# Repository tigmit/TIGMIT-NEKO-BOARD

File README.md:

# TIGMIT NEKO BOARD 

HEY fellow nerd :3
thanks for checking out my project hehe

This is a one man project trying to create (my) ultimate keyboard. taylored to the personal needs of a software developer with a thing for cute and weeby shit... hence the name :P 

the project features 

- 79 keys in a kind of.. compact TKL arrangement.
- a 240 x 240 round Display
- rotary encoder
- analog slider
- fully controllable RGB for each key
- hot swappable switches
- fully custom Firmware (feel free to reuse for your project)
- wireless operation via Bluetooth
- a fully functioal shell with ato completion

to enable the NEKO SHELL go to debugSettings.hpp and enable ```#define DEVMODE ```

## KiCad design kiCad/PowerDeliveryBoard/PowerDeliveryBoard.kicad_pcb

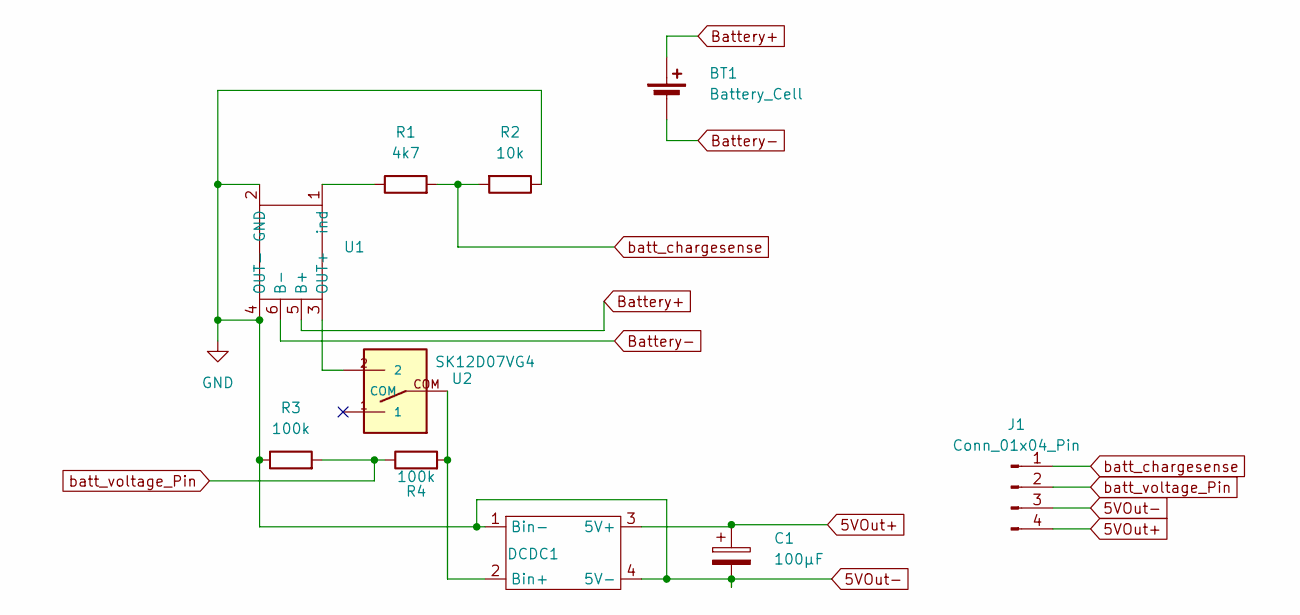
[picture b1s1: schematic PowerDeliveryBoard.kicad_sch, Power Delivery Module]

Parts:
BT1: Battery_Cell; battery solder pins
C1: 100µF; CP_Elec_6.3x5.2
DCDC1: DCDC-Converter
J1: Conn_01x04_Pin; PinHeader_1x04_P2.54mm_Vertical
R1: 4k7; R_Axial_DIN0204_L3.6mm_D1.6mm_P7.62mm_Horizontal
R2: 10k; R_Axial_DIN0204_L3.6mm_D1.6mm_P7.62mm_Horizontal
R3, R4: 100k; R_Axial_DIN0204_L3.6mm_D1.6mm_P7.62mm_Horizontal
U1: TP4056-18650
U2: SK12D07VG4

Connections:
5VOut+: C1.1, DCDC1.3 (5V+), J1.4
5VOut-: C1.2, DCDC1.1 (Bin-), DCDC1.4 (5V-), J1.3, R2.1, R3.1, U1.2 (GND), U1.4 (OUT-)
Battery+: BT1.1 (+), U1.5 (B+)
Battery-: BT1.2 (-), U1.6 (B-)
unnamed: DCDC1.2 (Bin+), R4.2, U2.COM
unnamed: U1.3 (OUT+), U2.2
unnamed: R1.1, U1.1 (ind)
batt_chargesense: J1.1, R1.2, R2.2
batt_voltage_Pin: J1.2, R3.2, R4.1

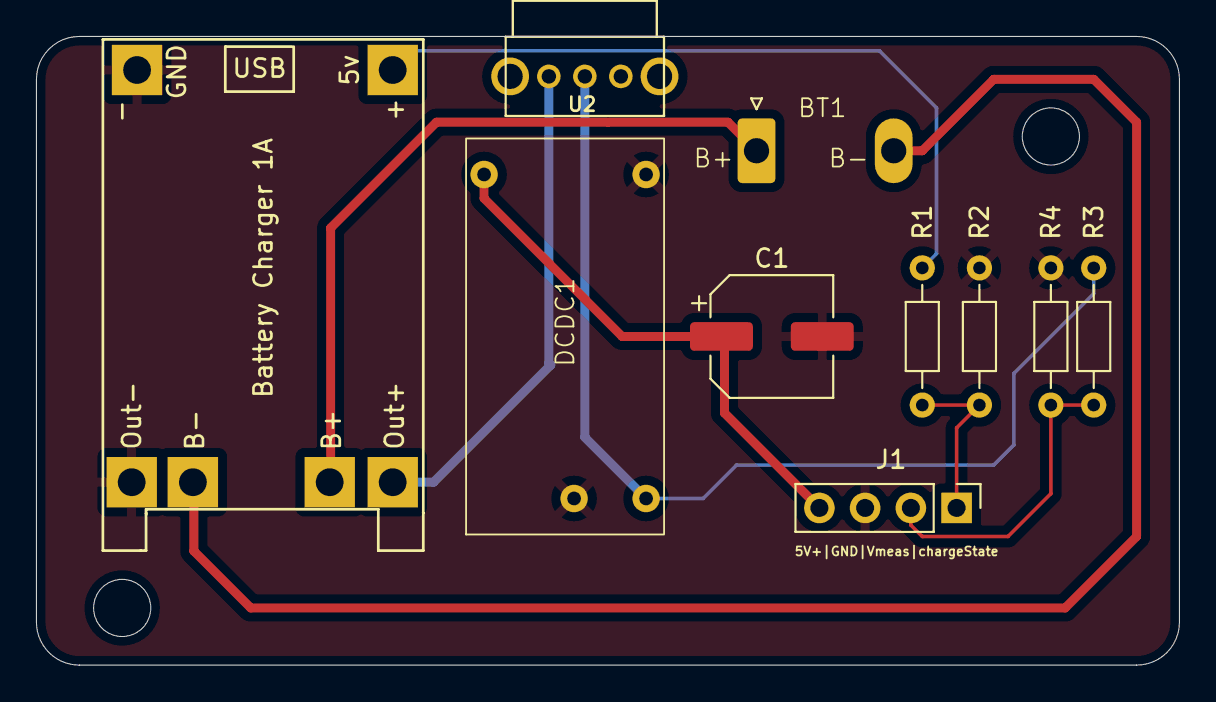
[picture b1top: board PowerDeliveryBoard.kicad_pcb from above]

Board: 2 copper layers, 63.5 x 34.9 mm, 10 parts (0 on the bottom side), 9 nets.

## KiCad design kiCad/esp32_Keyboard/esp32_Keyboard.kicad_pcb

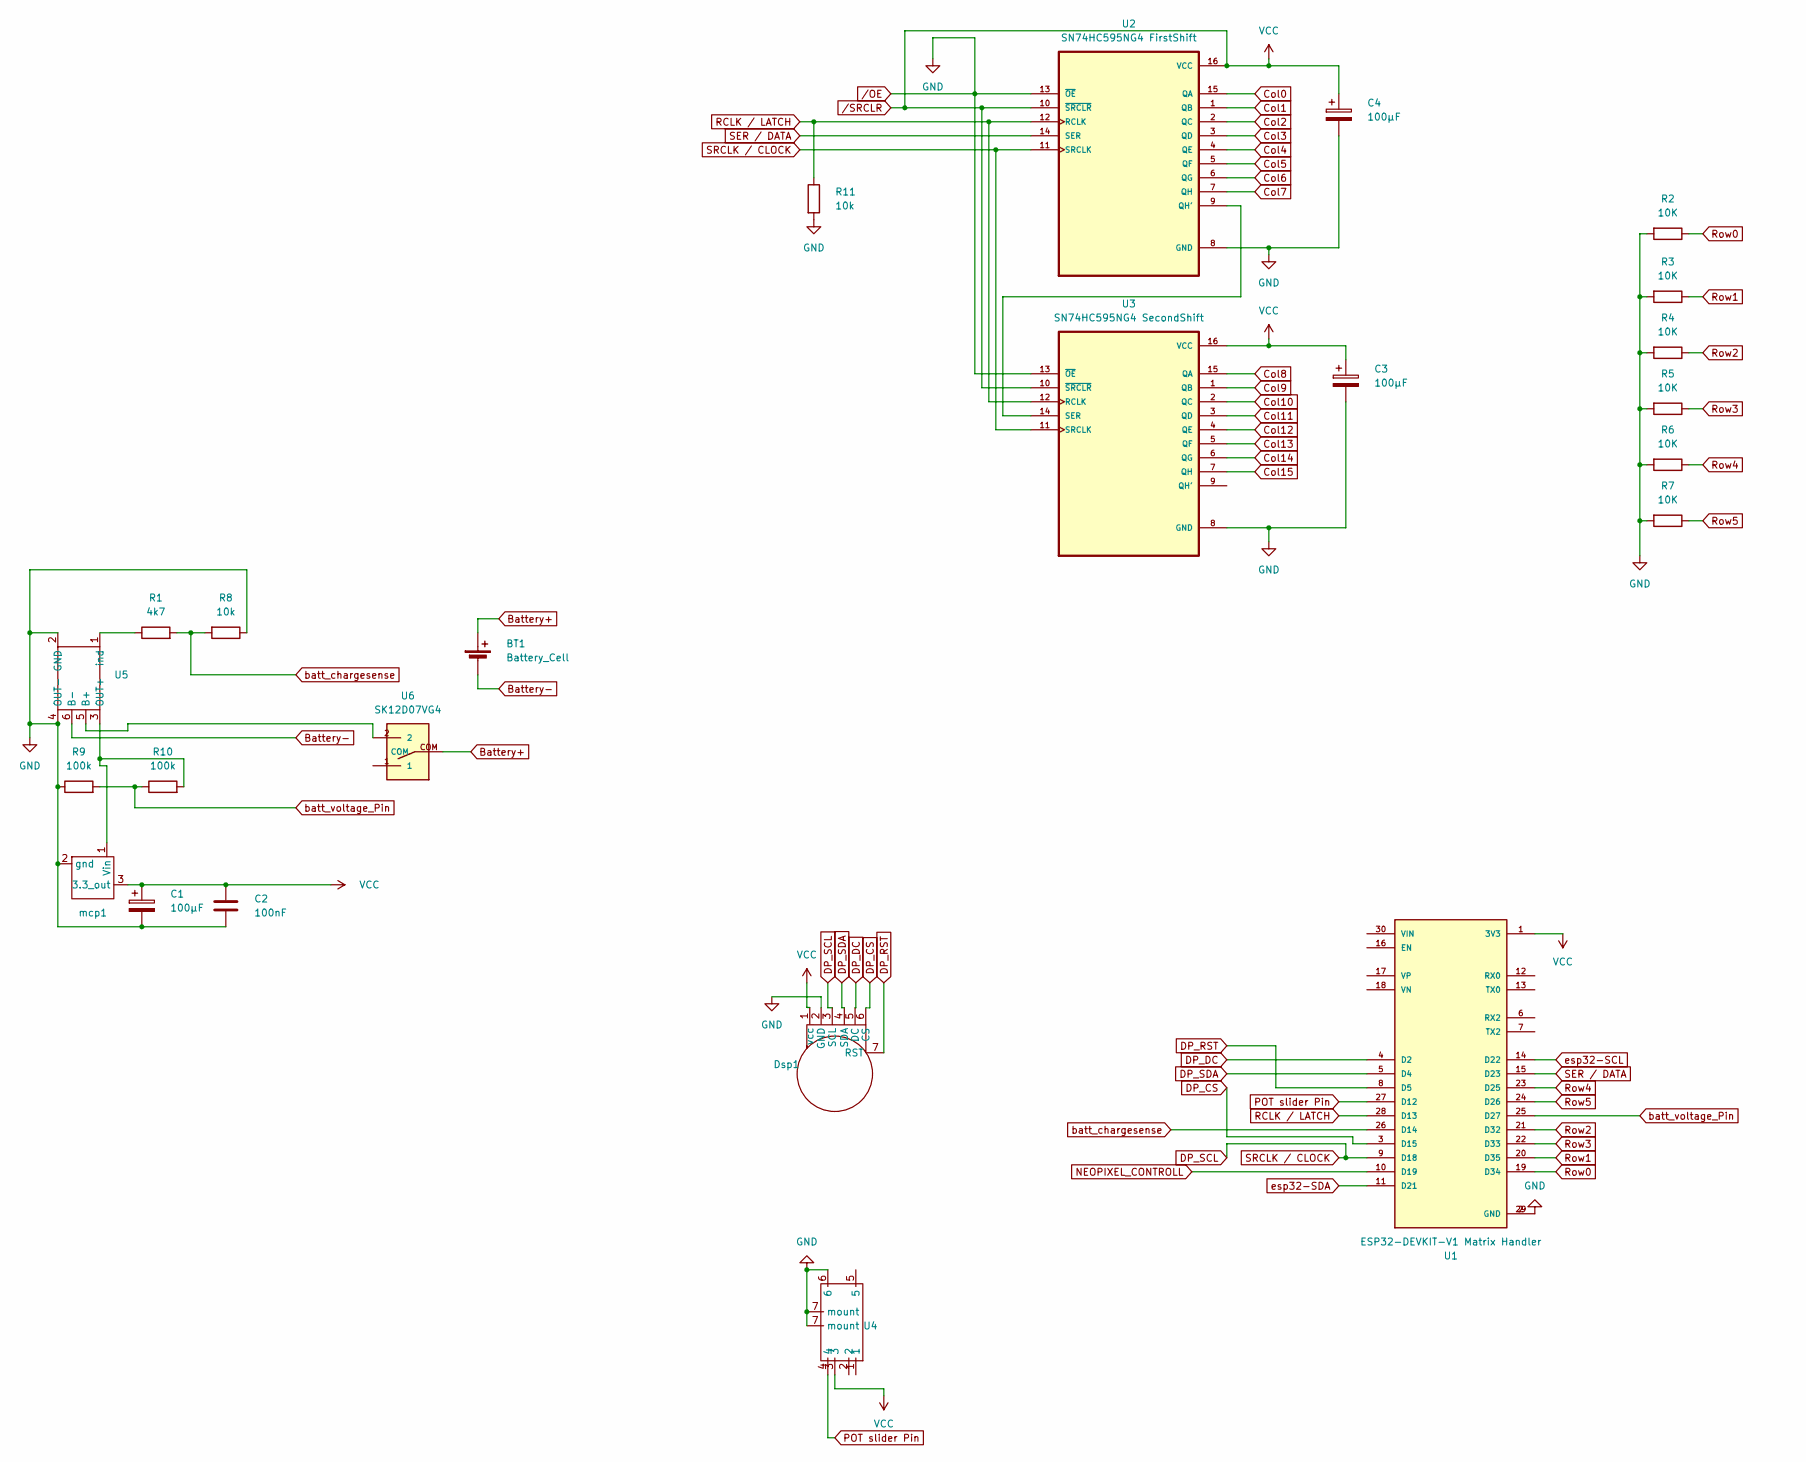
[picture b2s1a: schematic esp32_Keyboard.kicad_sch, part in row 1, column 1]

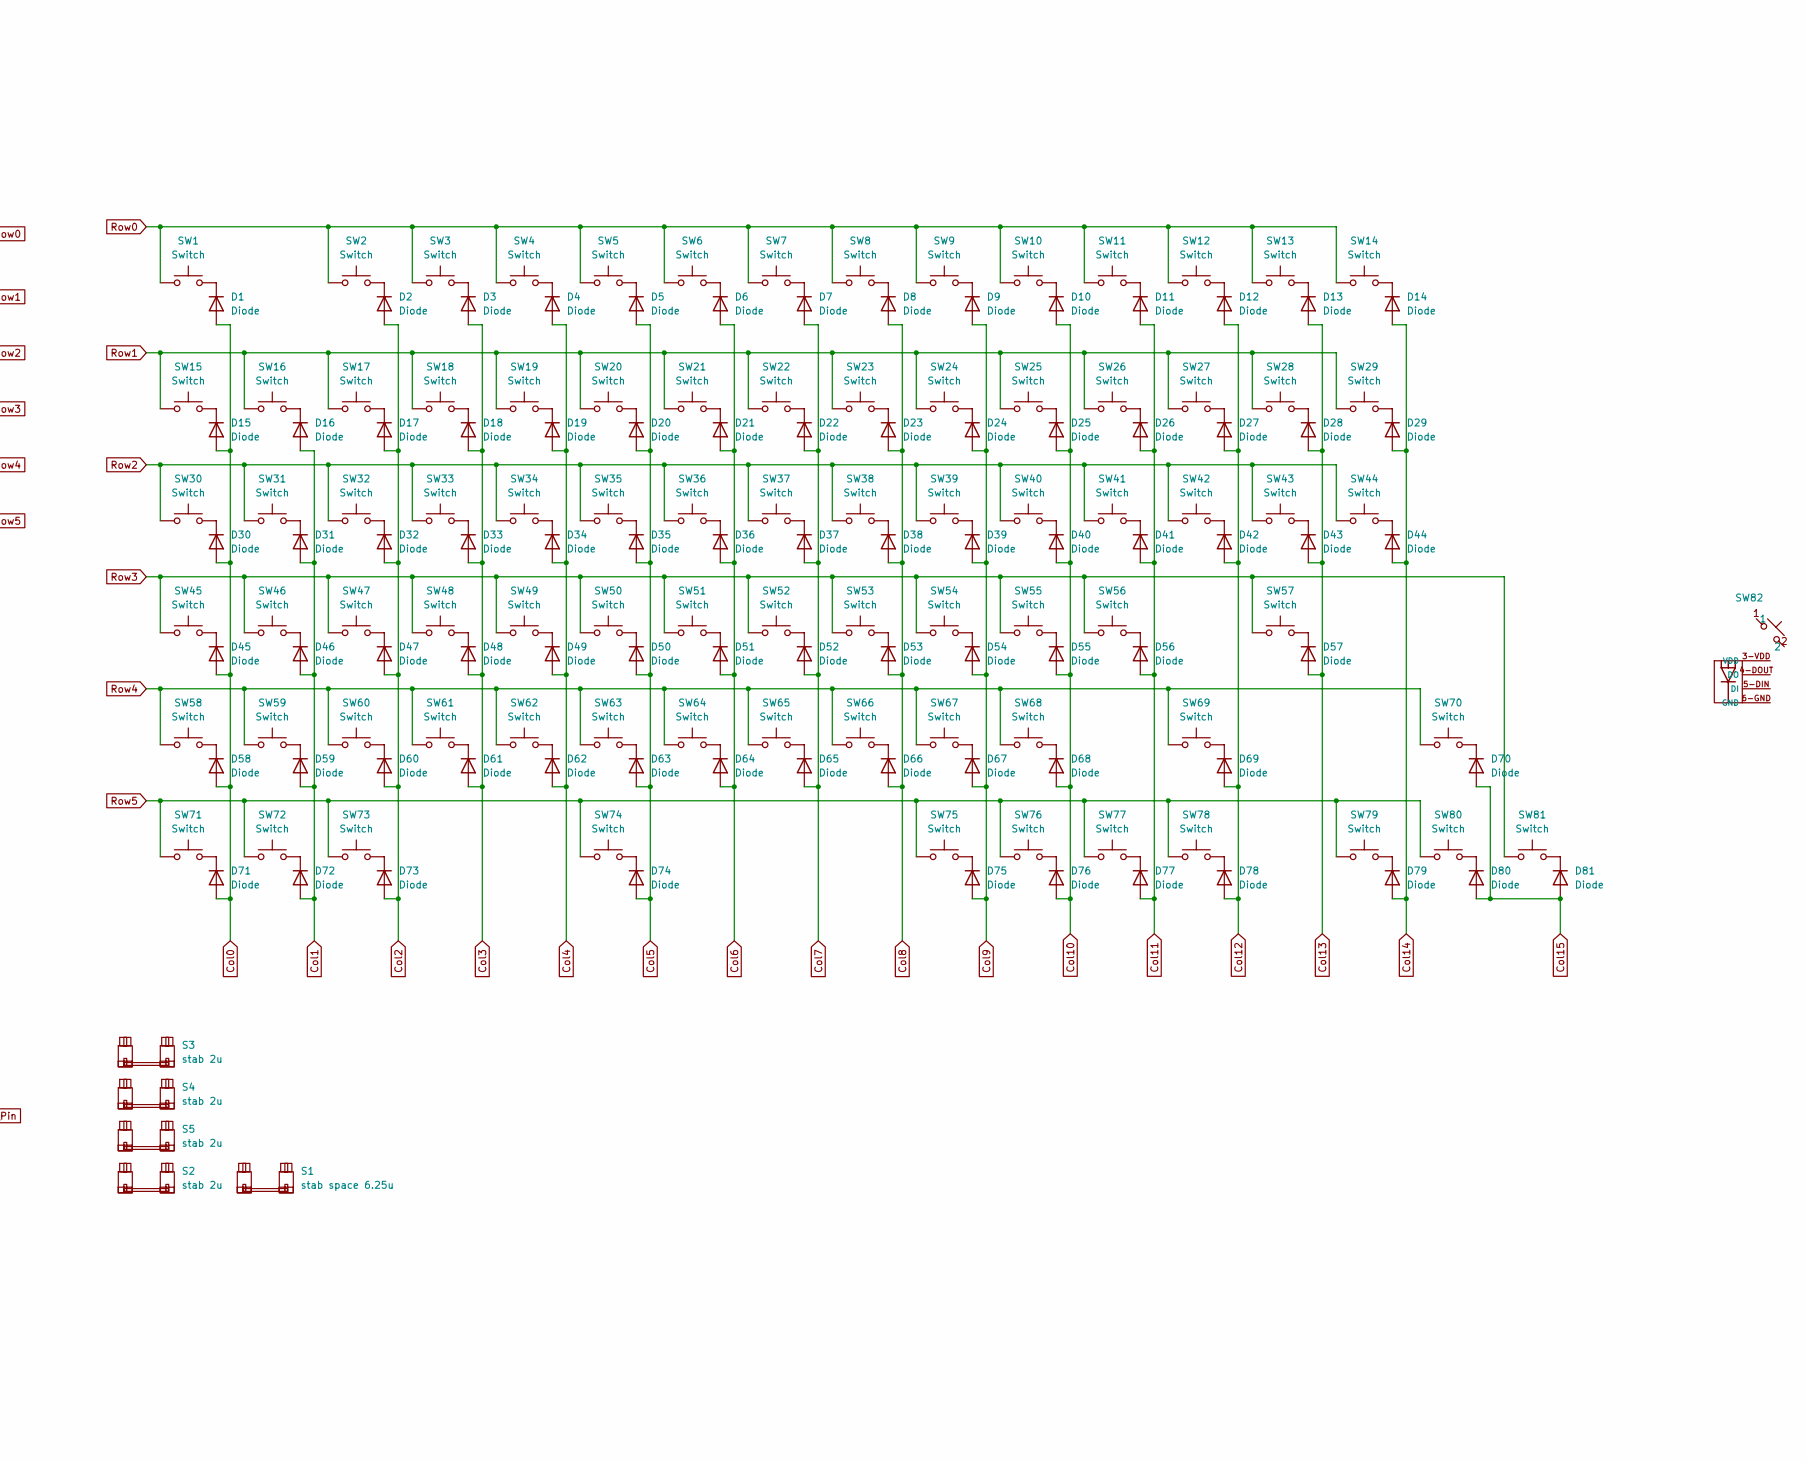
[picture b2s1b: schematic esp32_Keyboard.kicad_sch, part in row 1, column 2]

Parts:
BT1: Battery_Cell; battery solder pins
C1, C3, C4: 100µF; CP_Radial_D10.0mm_P2.50mm
C2: 100nF; C_Rect_L7.0mm_W2.5mm_P5.00mm
D1, D2, D3, D4, D5, D6, D7, D8, D9, D10, D11, D12, D13, D14, D15, D16, D17, D18, D19, D20, D21, D22, D23, D24, D25, D26, D27, D28, D29, D30, D31, D32, D33, D34, D35, D36, D37, D38, D39, D40, D41, D42, D43, D44, D45, D46, D47, D48, D49, D50, D51, D52, D53, D54, D55, D56, D57, D58, D59, D60, D61, D62, D63, D64, D65, D66, D67, D68, D69, D70, D71, D72, D73, D74, D75, D76, D77, D78, D79, D80, D81: Diode; Diode_SOD-123
Dsp1: PinHeader_1x07_P2.54mm_Vertical
R1: 4k7; R_Axial_DIN0204_L3.6mm_D1.6mm_P7.62mm_Horizontal
R2, R3, R4, R5, R6, R7: 10K; R_Axial_DIN0204_L3.6mm_D1.6mm_P7.62mm_Horizontal
R8, R11: 10k; R_Axial_DIN0204_L3.6mm_D1.6mm_P7.62mm_Horizontal
R9, R10: 100k; R_Axial_DIN0204_L3.6mm_D1.6mm_P7.62mm_Horizontal
S1: stab space 6.25u; STAB_MX_6.25u
S2, S3, S4, S5: stab 2u; STAB_MX_2u
SW1, SW2, SW3, SW4, SW5, SW6, SW7, SW8, SW9, SW10, SW11, SW12, SW13, SW14, SW15, SW16, SW17, SW18, SW19, SW20, SW21, SW22, SW23, SW24, SW25, SW26, SW27, SW29, SW31, SW32, SW33, SW34, SW35, SW36, SW37, SW38, SW39, SW40, SW41, SW42, SW44, SW46, SW47, SW48, SW49, SW50, SW51, SW52, SW53, SW54, SW55, SW56, SW59, SW60, SW61, SW62, SW63, SW64, SW65, SW66, SW67, SW68, SW70, SW79, SW80, SW81: Switch; Hotswap_MX_1.00u
SW28: Switch; Hotswap_MX_2.00u
SW30, SW43: Switch; Hotswap_MX_1.50u
SW45: Switch; Hotswap_MX_1.75u
SW57, SW58: Switch; Hotswap_MX_2.25u
SW69: Switch; Hotswap_MX_2.75u
SW71, SW72, SW73, SW75, SW76, SW77, SW78: Switch; Hotswap_MX_1.25u
SW74: Switch; Hotswap_MX_6.25u
SW82: hotswap socket with neopixel
U1: ESP32-DEVKIT-V1 Matrix Handler; ESP32 Vroom Devkit V1; PARTREV N/A
U2: SN74HC595NG4 FirstShift; SNH Shift register
U3: SN74HC595NG4 SecondShift; SNH Shift register
U4: b103 multichannel fader pot
U5: TP4056-18650
U6: SK12D07VG4
mcp1: MCP1700 3.3V

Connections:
Battery+: BT1.1 (+), U6.COM
Battery-: BT1.2 (-), U5.6 (B-)
Col0: D1.2 (A), D15.2 (A), D30.2 (A), D45.2 (A), D58.2 (A), D71.2 (A), U2.15 (QA)
Col1: D16.2 (A), D31.2 (A), D46.2 (A), D59.2 (A), D72.2 (A), U2.1 (QB)
Col2: D2.2 (A), D17.2 (A), D32.2 (A), D47.2 (A), D60.2 (A), D73.2 (A), U2.2 (QC)
Col3: D3.2 (A), D18.2 (A), D33.2 (A), D48.2 (A), D61.2 (A), U2.3 (QD)
Col4: D4.2 (A), D19.2 (A), D34.2 (A), D49.2 (A), D62.2 (A), U2.4 (QE)
Col5: D5.2 (A), D20.2 (A), D35.2 (A), D50.2 (A), D63.2 (A), D74.2 (A), U2.5 (QF)
Col6: D6.2 (A), D21.2 (A), D36.2 (A), D51.2 (A), D64.2 (A), U2.6 (QG)
Col7: D7.2 (A), D22.2 (A), D37.2 (A), D52.2 (A), D65.2 (A), U2.7 (QH)
Col8: D8.2 (A), D23.2 (A), D38.2 (A), D53.2 (A), D66.2 (A), U3.15 (QA)
Col9: D9.2 (A), D24.2 (A), D39.2 (A), D54.2 (A), D67.2 (A), D75.2 (A), U3.1 (QB)
Col10: D10.2 (A), D25.2 (A), D40.2 (A), D55.2 (A), D68.2 (A), D76.2 (A), U3.2 (QC)
Col11: D11.2 (A), D26.2 (A), D41.2 (A), D56.2 (A), D77.2 (A), U3.3 (QD)
Col12: D12.2 (A), D27.2 (A), D42.2 (A), D69.2 (A), D78.2 (A), U3.4 (QE)
Col13: D13.2 (A), D28.2 (A), D43.2 (A), D57.2 (A), U3.5 (QF)
Col14: D14.2 (A), D29.2 (A), D44.2 (A), D79.2 (A), U3.6 (QG)
Col15: D70.2 (A), D80.2 (A), D81.2 (A), U3.7 (QH)
DP_CS: Dsp1.6 (CS), U1.3 (D15)
DP_DC: Dsp1.5 (DC), U1.4 (D2)
DP_RST: Dsp1.7 (RST), U1.8 (D5)
DP_SCL: Dsp1.3 (SCL), U1.9 (D18), U2.11 (SRCLK), U3.11 (SRCLK)
DP_SDA: Dsp1.4 (SDA), U1.5 (D4)
NEOPIXEL_CONTROLL: U1.10 (D19)
unnamed: D1.1 (K), SW1.2
unnamed: D2.1 (K), SW2.2
unnamed: D3.1 (K), SW3.2
unnamed: D4.1 (K), SW4.2
unnamed: D5.1 (K), SW5.2
unnamed: D6.1 (K), SW6.2
unnamed: D7.1 (K), SW7.2
unnamed: D8.1 (K), SW8.2
unnamed: D9.1 (K), SW9.2
unnamed: D10.1 (K), SW10.2
unnamed: D11.1 (K), SW11.2
unnamed: D12.1 (K), SW12.2
unnamed: D13.1 (K), SW13.2
unnamed: D14.1 (K), SW14.2
unnamed: D15.1 (K), SW15.2
unnamed: D16.1 (K), SW16.2
unnamed: D17.1 (K), SW17.2
unnamed: D18.1 (K), SW18.2
unnamed: D19.1 (K), SW19.2
unnamed: D20.1 (K), SW20.2
unnamed: D21.1 (K), SW21.2
unnamed: D22.1 (K), SW22.2
unnamed: D23.1 (K), SW23.2
unnamed: D24.1 (K), SW24.2
unnamed: D25.1 (K), SW25.2
unnamed: D26.1 (K), SW26.2
unnamed: D27.1 (K), SW27.2
unnamed: D28.1 (K), SW28.2
unnamed: D29.1 (K), SW29.2
unnamed: D30.1 (K), SW30.2
unnamed: D31.1 (K), SW31.2
unnamed: D32.1 (K), SW32.2
unnamed: D33.1 (K), SW33.2
unnamed: D34.1 (K), SW34.2
unnamed: D35.1 (K), SW35.2
unnamed: D36.1 (K), SW36.2
unnamed: D37.1 (K), SW37.2
unnamed: D38.1 (K), SW38.2
unnamed: D39.1 (K), SW39.2
unnamed: D40.1 (K), SW40.2
unnamed: D41.1 (K), SW41.2
unnamed: D42.1 (K), SW42.2
unnamed: D43.1 (K), SW43.2
unnamed: D44.1 (K), SW44.2
unnamed: D45.1 (K), SW45.2
unnamed: D46.1 (K), SW46.2
unnamed: D47.1 (K), SW47.2
unnamed: D48.1 (K), SW48.2
unnamed: D49.1 (K), SW49.2
unnamed: D50.1 (K), SW50.2
unnamed: D51.1 (K), SW51.2
unnamed: D52.1 (K), SW52.2
unnamed: D53.1 (K), SW53.2
unnamed: D54.1 (K), SW54.2
unnamed: D55.1 (K), SW55.2
unnamed: D56.1 (K), SW56.2
unnamed: D57.1 (K), SW57.2
unnamed: D58.1 (K), SW58.2
unnamed: D59.1 (K), SW59.2
unnamed: D60.1 (K), SW60.2
unnamed: D61.1 (K), SW61.2
unnamed: D62.1 (K), SW62.2
unnamed: D63.1 (K), SW63.2
unnamed: D64.1 (K), SW64.2
unnamed: D65.1 (K), SW65.2
unnamed: D66.1 (K), SW66.2
unnamed: D67.1 (K), SW67.2
unnamed: D68.1 (K), SW68.2
unnamed: D69.1 (K), SW69.2
unnamed: D70.1 (K), SW70.2
unnamed: D71.1 (K), SW71.2
unnamed: D72.1 (K), SW72.2
unnamed: D73.1 (K), SW73.2
unnamed: D74.1 (K), SW74.2
unnamed: D75.1 (K), SW75.2
unnamed: D76.1 (K), SW76.2
unnamed: D77.1 (K), SW77.2
unnamed: D78.1 (K), SW78.2
unnamed: D79.1 (K), SW79.2
unnamed: D80.1 (K), SW80.2
unnamed: D81.1 (K), SW81.2
unnamed: U2.9 (QH'), U3.14 (SER)
unnamed: U5.5 (B+), U6.2
unnamed: R10.2, U5.3 (OUT+), mcp1.1 (Vin)
unnamed: R1.1, U5.1 (ind)
POT slider Pin: U1.27 (D12), U4.4
RCLK / LATCH: R11.1, U1.28 (D13), U2.12 (RCLK), U3.12 (RCLK)
Row0: R2.1, SW1.1, SW2.1, SW3.1, SW4.1, SW5.1, SW6.1, SW7.1, SW8.1, SW9.1, SW10.1, SW11.1, SW12.1, SW13.1, SW14.1, U1.19 (D34)
Row1: R3.1, SW15.1, SW16.1, SW17.1, SW18.1, SW19.1, SW20.1, SW21.1, SW22.1, SW23.1, SW24.1, SW25.1, SW26.1, SW27.1, SW28.1, SW29.1, U1.20 (D35)
Row2: R4.1, SW30.1, SW31.1, SW32.1, SW33.1, SW34.1, SW35.1, SW36.1, SW37.1, SW38.1, SW39.1, SW40.1, SW41.1, SW42.1, SW43.1, SW44.1, U1.21 (D32)
Row3: R5.1, SW45.1, SW46.1, SW47.1, SW48.1, SW49.1, SW50.1, SW51.1, SW52.1, SW53.1, SW54.1, SW55.1, SW56.1, SW57.1, SW81.1, U1.22 (D33)
Row4: R6.1, SW58.1, SW59.1, SW60.1, SW61.1, SW62.1, SW63.1, SW64.1, SW65.1, SW66.1, SW67.1, SW68.1, SW69.1, SW70.1, U1.23 (D25)
Row5: R7.1, SW71.1, SW72.1, SW73.1, SW74.1, SW75.1, SW76.1, SW77.1, SW78.1, SW79.1, SW80.1, U1.24 (D26)
SER / DATA: U1.15 (D23), U2.14 (SER)
batt_chargesense: R1.2, R8.2, U1.26 (D14)
batt_voltage_Pin: R9.2, R10.1, U1.25 (D27)
esp32-SCL: U1.14 (D22)
esp32-SDA: U1.11 (D21)
/OE: C1.2, C2.2, C3.2, C4.2, Dsp1.2 (GND), R2.2, R3.2, R4.2, R5.2, R6.2, R7.2, R8.1, R9.1, R11.2, U1.2 (GND), U1.29 (GND), U2.8 (GND), U2.13 (~OE), U3.8 (GND), U3.13 (~OE), U4.6, U4.7 (mount), U5.2 (GND), U5.4 (OUT-), mcp1.2 (gnd)
/SRCLR: C1.1, C2.1, C3.1, C4.1, Dsp1.1 (vcc), U1.1 (3V3), U2.10 (~SRCLR), U2.16 (VCC), U3.10 (~SRCLR), U3.16 (VCC), U4.3, mcp1.3 (3.3_out)

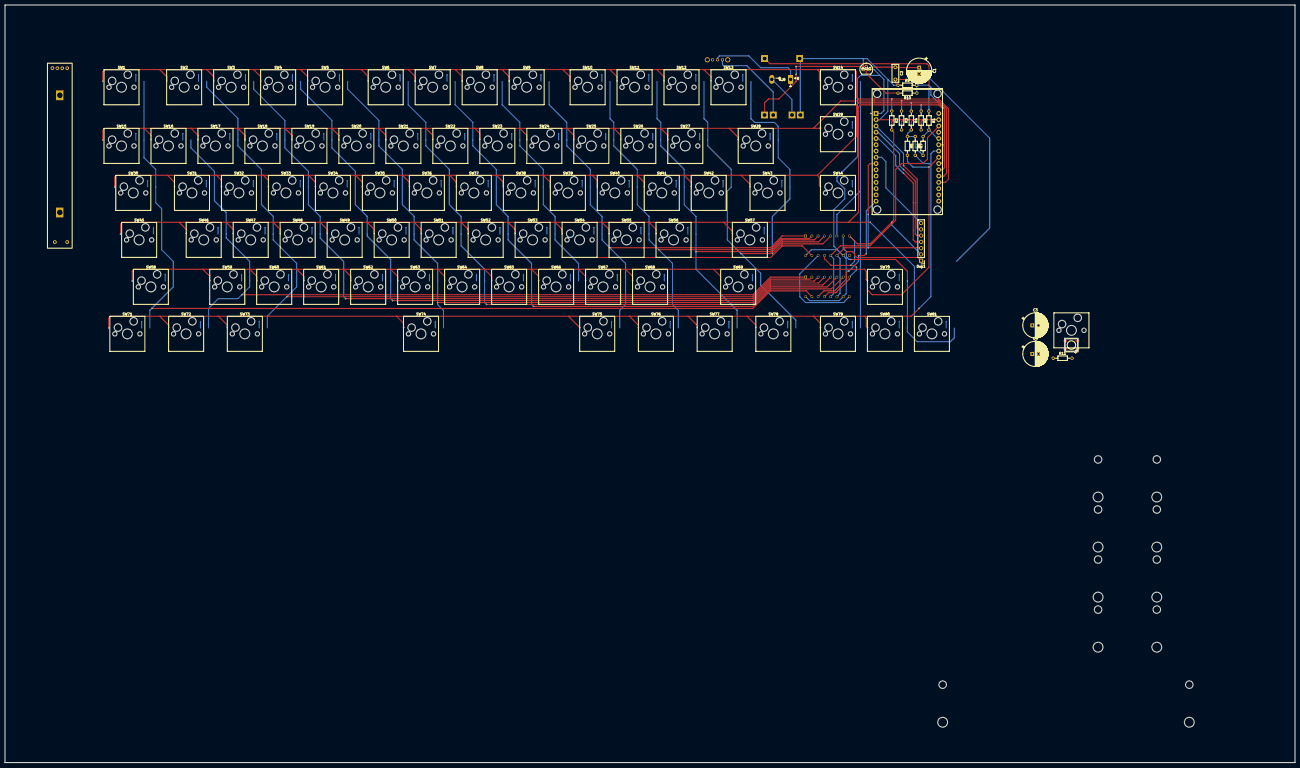
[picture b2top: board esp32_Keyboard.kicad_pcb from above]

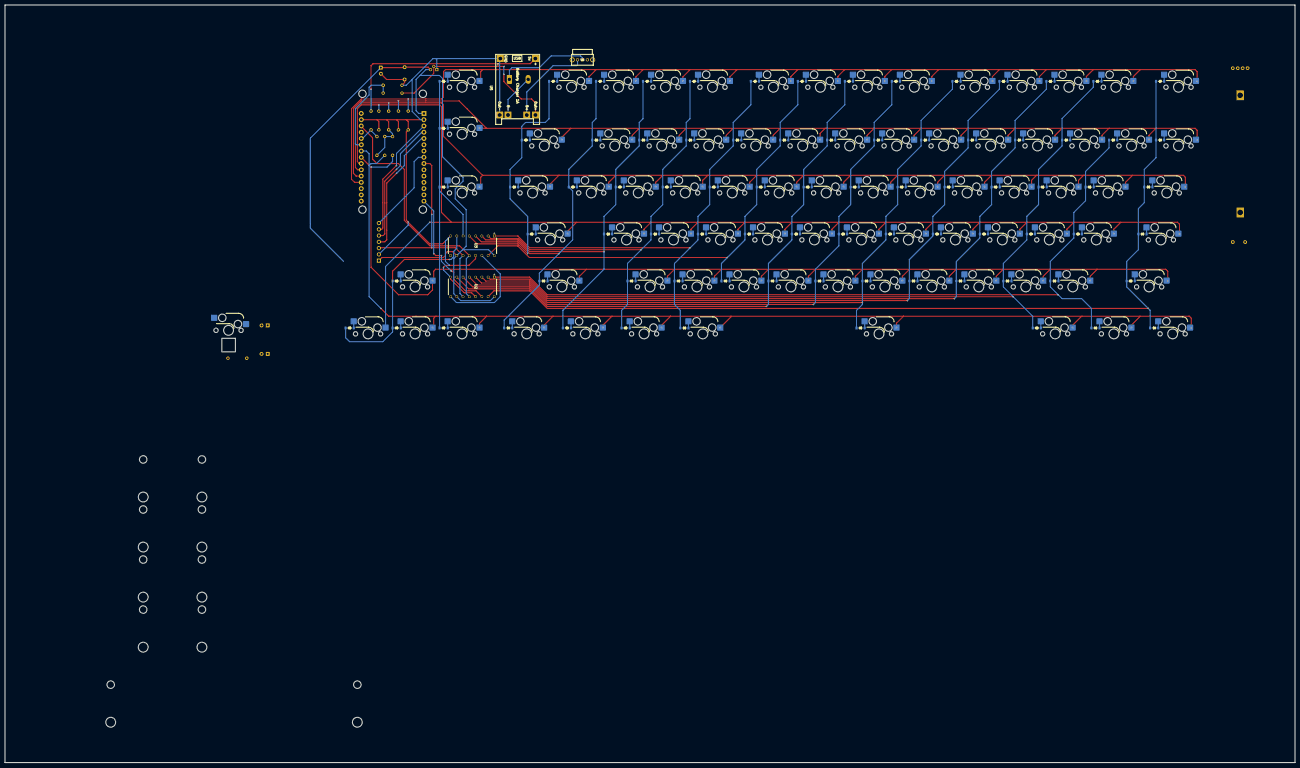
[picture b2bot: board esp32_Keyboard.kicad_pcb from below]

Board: 2 copper layers, 523.1 x 307.2 mm, 192 parts (85 on the bottom side), 121 nets.

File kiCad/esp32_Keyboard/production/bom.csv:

Designator,Footprint,Quantity,Value,LCSC Part #
"D1, D10, D11, D12, D13, D14, D15, D16, D17, D18, D19, D2, D20, D21, D22, D23, D24, D25, D26, D27, D28, D29, D3, D30, D31, D32, D33, D34, D35, D36, D37, D38, D39, D4, D40, D41, D42, D43, D44, D45, D46, D47, D48, D49, D5, D50, D51, D52, D53, D54, D55, D56, D57, D58, D59, D6, D60, D61, D62, D63, D64, D65, D66, D67, D68, D69, D7, D70, D71, D72, D73, D74, D75, D76, D77, D78, D79, D8, D80, D81, D9",Diode_SOD-123,81,Diode,
Dsp1,PinHeader_1x07_P2.54mm_Vertical,1,~,
"R2, R3, R4, R5, R6, R7",R_Axial_DIN0204_L3.6mm_D1.6mm_P7.62mm_Horizontal,6,10K,
S1,STAB_MX_2.25u,1,stab L shift 2.25u,
S2,STAB_MX_6.25u,1,stab space 6.25u,
S3,STAB_MX_2.75u,1,stab R shift 2.75u,
S4,STAB_MX_2.25u,1,stab enter 2.25u,
S5,STAB_MX_2u,1,stab backspace 2u,
"SW1, SW10, SW11, SW12, SW13, SW14, SW15, SW16, SW17, SW18, SW19, SW2, SW20, SW21, SW22, SW23, SW24, SW25, SW26, SW27, SW29, SW3, SW31, SW32, SW33, SW34, SW35, SW36, SW37, SW38, SW39, SW4, SW40, SW41, SW42, SW44, SW46, SW47, SW48, SW49, SW5, SW50, SW51, SW52, SW53, SW54, SW55, SW56, SW59, SW6, SW60, SW61, SW62, SW63, SW64, SW65, SW66, SW67, SW68, SW7, SW70, SW79, SW8, SW80, SW81, SW9",Hotswap_MX_1.00u,66,Switch,
SW28,Hotswap_MX_2.00u,1,Switch,
"SW30, SW43",Hotswap_MX_1.50u,2,Switch,
SW45,Hotswap_MX_1.75u,1,Switch,
"SW57, SW58",Hotswap_MX_2.25u,2,Switch,
SW69,Hotswap_MX_2.75u,1,Switch,
"SW71, SW72, SW73, SW75, SW76, SW77, SW78",Hotswap_MX_1.25u,7,Switch,
SW74,Hotswap_MX_6.25u,1,Switch,
U1,MODULE_ESP32_DEVKIT_V1,1,ESP32-DEVKIT-V1 Matrix Handler,
U2,DIP794W45P254L1969H508Q16,1,SN74HC595NG4 FirstShift,
U3,DIP794W45P254L1969H508Q16,1,SN74HC595NG4 SecondShift,
U4,b103 multichannel fader pot,1,~,
U5,MODULE_ESP32_DEVKIT_V1,1,ESP32-DEVKIT-V1 DisplayHandler,

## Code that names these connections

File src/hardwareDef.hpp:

/**
 * hardwareDef.hpp
 * brief   : defining the pins for the key matrix
 * created : 25.05.2024
 * creator : @tigmit
 * Licence : opensource
 */
#pragma once

// Define on and off values
#define OFF 0
#define ON 1

// Pin Definitions
#define row1 25
#define row2 26
#define row3 27
#define row4 14
#define row5 12
#define row6 13

#define col1 33
#define col2 32
#define col3 35
#define col4 34
#define col5 39
#define col6 36
#define col7 23
#define col8 22
#define col9 21
#define col10 19
#define col11 18
#define col12 5
#define col13 17
#define col14 16
#define col15 4
#define col16 2
#define col17 15

// Matrix setup
#define numRows 6
#define numCols 17
#define numLayers 2

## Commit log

2024-05-25 configure tasks
2024-05-26 update project settings
2024-05-26 define hardware GWPIO pins
2024-05-26 introduce KeyboardHandler
2024-05-26 update kbdHandler vareable
2024-05-26 add first basic layout
2024-05-26 initialize basic keyboard functionality
2024-05-26 pathfinder commit: beautify wait for connection
2024-05-26 move HW define files and create files for display handler
2024-05-26 add framework for GC9A01 Display
2024-05-27 create keyboard layout
2024-05-28 finished layout circuit baord V1
2024-05-28 current status not tested. waiting for hardware PCB
2024-05-29 finished PCB design
2024-05-30 add spi lib to gitignore
2024-05-31 kicad stuff
2024-05-31 display lib compiling state
2024-06-11 commit current work
2024-06-11 save 2
2024-06-12 keyboard Firmware IS RUNNING BONGO MODEEEEEE
2024-06-16 working state with new wallpaper
2024-06-19 added ecoder and LED Support
2024-06-19 refactor a little bit
2024-06-26 saving kicad progress HW rev2
2024-06-26 introducing RGB handler
2024-06-26 update documentation
2024-06-26 remove unneded uml in main doc
2024-06-27 assert pointers
2024-06-27 latch via SR handler
2024-06-27 namin classes conform to google style guide
2024-06-27 comment fix
2024-06-29 remove a comment
2024-07-06 working version for tigmit board rev1 release candidate
2024-07-21 hardware design updates
2024-07-23 menu working + LED Screen immage
2024-07-28 introducing FSM statemachine
2024-07-28 statemachine fully implemented
2024-08-02 create all 3d Case files for order rev V1 compatible with pcb Rev2
2024-08-02 ontrocuduce documentation and readme
2024-08-02 forgott to close kicad
2024-08-02 introduce buildpipeline
2024-08-02 edit includes
2024-08-03 move espi lib locally to avoid losing user settings
2024-08-03 make pipeline run on release
2024-08-03 make pipeline run in dev and release
2024-08-03 Shell art and updated debug settings
2024-08-04 introduce DEV SHELL
2024-08-04 introduce model- beautify main and new shell command
2024-08-05 rgb settings in persistent memory
2024-08-05 forgott return in non void funtion
2024-08-07 persistent rgb config + rgb accept prompt
2024-08-07 make RGB single adressable baz mappting to rows and colls
2024-08-10 introduce HW timer handler
2024-08-15 add idle screen
2024-08-15 add some pictures and organize them a bit
2024-08-15 first shot introducing SliderHandler
2024-08-15 init slider handler in main
2024-08-15 change comment
2024-08-17 add some headder descritions
2024-08-18 devcontainer playground
2024-08-18 build docker container compile OK upload not working
2024-08-19 make Statemachine BETTER!
